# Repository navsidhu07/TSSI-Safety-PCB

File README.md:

# Tractive System Status Indicator Power & Safety Board

## Project Overview

A custom safety and fault detection PCB designed in KiCad
as part of the Formula SAE Electrical Team onboarding
project at the University of Texas at Dallas.

The PCB was designed from provided system requirements
to implement power protection, input signal conditioning,
hardware-based fault detection, and fault latching logic.

The schematic, component selection, PCB layout, and routing
were independently developed as part of the onboarding project.

## Key Features

- 12 V battery power input
- PMOS-based reverse polarity protection
- TVS diode transient voltage suppression
- 5 V voltage regulation
- BMS and IMD fault signal conditioning
- Voltage divider and RC filtering circuits
- NAND-based fault detection logic
- Hardware-based SR latch
- Power-on reset circuitry
- Custom two-layer PCB designed in KiCad

## System Architecture

### Power Distribution

```mermaid
flowchart LR
    A[12 V Battery] --> B[PMOSFET]
    B --> C[Protected 12 V Rail]
    C --- D[TVS Diode]
    C --> E[5 V Regulator]
    E --> F[5 V Rail]
    F --> G[74HC00 VCC]
    F --> H[Output Header]
```

### Fault Detection and Latching

```mermaid
flowchart LR
    A[BMS Fault] --> B[Input Terminal]
    B --> C[Voltage Divider]
    C --> D[RC Filter]

    E[IMD Fault] --> F[Input Terminal]
    F --> G[Voltage Divider]
    G --> H[RC Filter]

    D --> I[Fault Detection]
    H --> I

    I --> J[SR Latch]
    K[Reset Circuit] --> J
    J --> L[Q / Q_NOT]
    L --> M[Output Header]
```

## Hardware Design

### Power Protection and Regulation

The power input circuitry incorporates a PMOS transistor
for reverse polarity protection and a TVS diode for
transient voltage suppression. A voltage regulator
provides a 5 V supply for the digital logic circuitry.

### Input Signal Conditioning

The BMS and IMD fault inputs are conditioned using
resistive voltage dividers and RC low-pass filters.
The voltage dividers reduce the input voltage to a
logic-compatible level, while the RC filters are
intended to reduce high-frequency noise.

### Fault Detection Logic

NAND-based combinational logic processes the conditioned
BMS and IMD fault signals to determine whether a fault
condition is present.

| BMS Input | IMD Input | System Condition |
| --- | --- | --- |
| HIGH | HIGH | No Fault |
| HIGH | LOW | Fault |
| LOW | HIGH | Fault |
| LOW | LOW | Fault |

### Hardware Fault Latch

A cross-coupled NAND-based SR latch is used to retain
a detected fault condition independently of subsequent
changes in the input signals.

A power-on reset circuit is included to initialize
the latch to a defined state during startup.

## PCB Design

The schematic and PCB layout were developed in KiCad.

### Design Considerations

- Power protection and distribution
- Input voltage level conditioning
- Signal filtering
- Hardware-based fault retention
- Power supply decoupling
- Component placement and signal routing
- Separate trace widths for power and logic signals

### Schematic

### Front Copper Layer

### Back Copper Layer

The native KiCad project, schematic, and PCB layout
files are available in the [Hardware](Hardware/) directory.

Additional component libraries are provided as ZIP
archives and can be extracted and imported into KiCad
as needed.

## Design Documentation

Handwritten engineering notes developed throughout
the design process are available in the
[Documentation](Documentation/) directory.

The documentation covers:

- Fault detection truth tables
- SR latch logic and circuit development
- Input voltage conditioning
- RC filtering
- Power distribution architecture
- PCB trace width selection

## Repository Structure

```
TSSI-Safety-PCB/
├── Hardware/
│   ├── pcb1.kicad_pro
│   ├── pcb1.kicad_sch
│   ├── pcb1.kicad_pcb
│   ├── pcb1.pdf
│   ├── SMBJ13A.zip
│   └── ul_SI4143DY-T1-GE3.zip
├── Documentation/
│   └── Design-Notes.pdf
└── README.md
```

## Project Status

The component selection, schematic design, PCB layout,
and routing have been completed in KiCad as part of
the Formula SAE Electrical Team onboarding project.
The PCB has not yet been fabricated or physically
validated. Future development would involve hardware
assembly, electrical testing, and verification of
the protection and fault detection circuitry.

## Future Improvements

- Fabricate and assemble the PCB
- Validate power protection circuitry
- Verify input conditioning and logic voltage levels
- Test fault detection and latching behavior
- Validate power-on reset timing and startup behavior

## Tools and Technologies

- KiCad
- PCB Design
- Digital Logic
- MOSFET Circuitry
- Voltage Regulation
- RC Filtering
- Hardware Fault Detection
- Sequential Logic

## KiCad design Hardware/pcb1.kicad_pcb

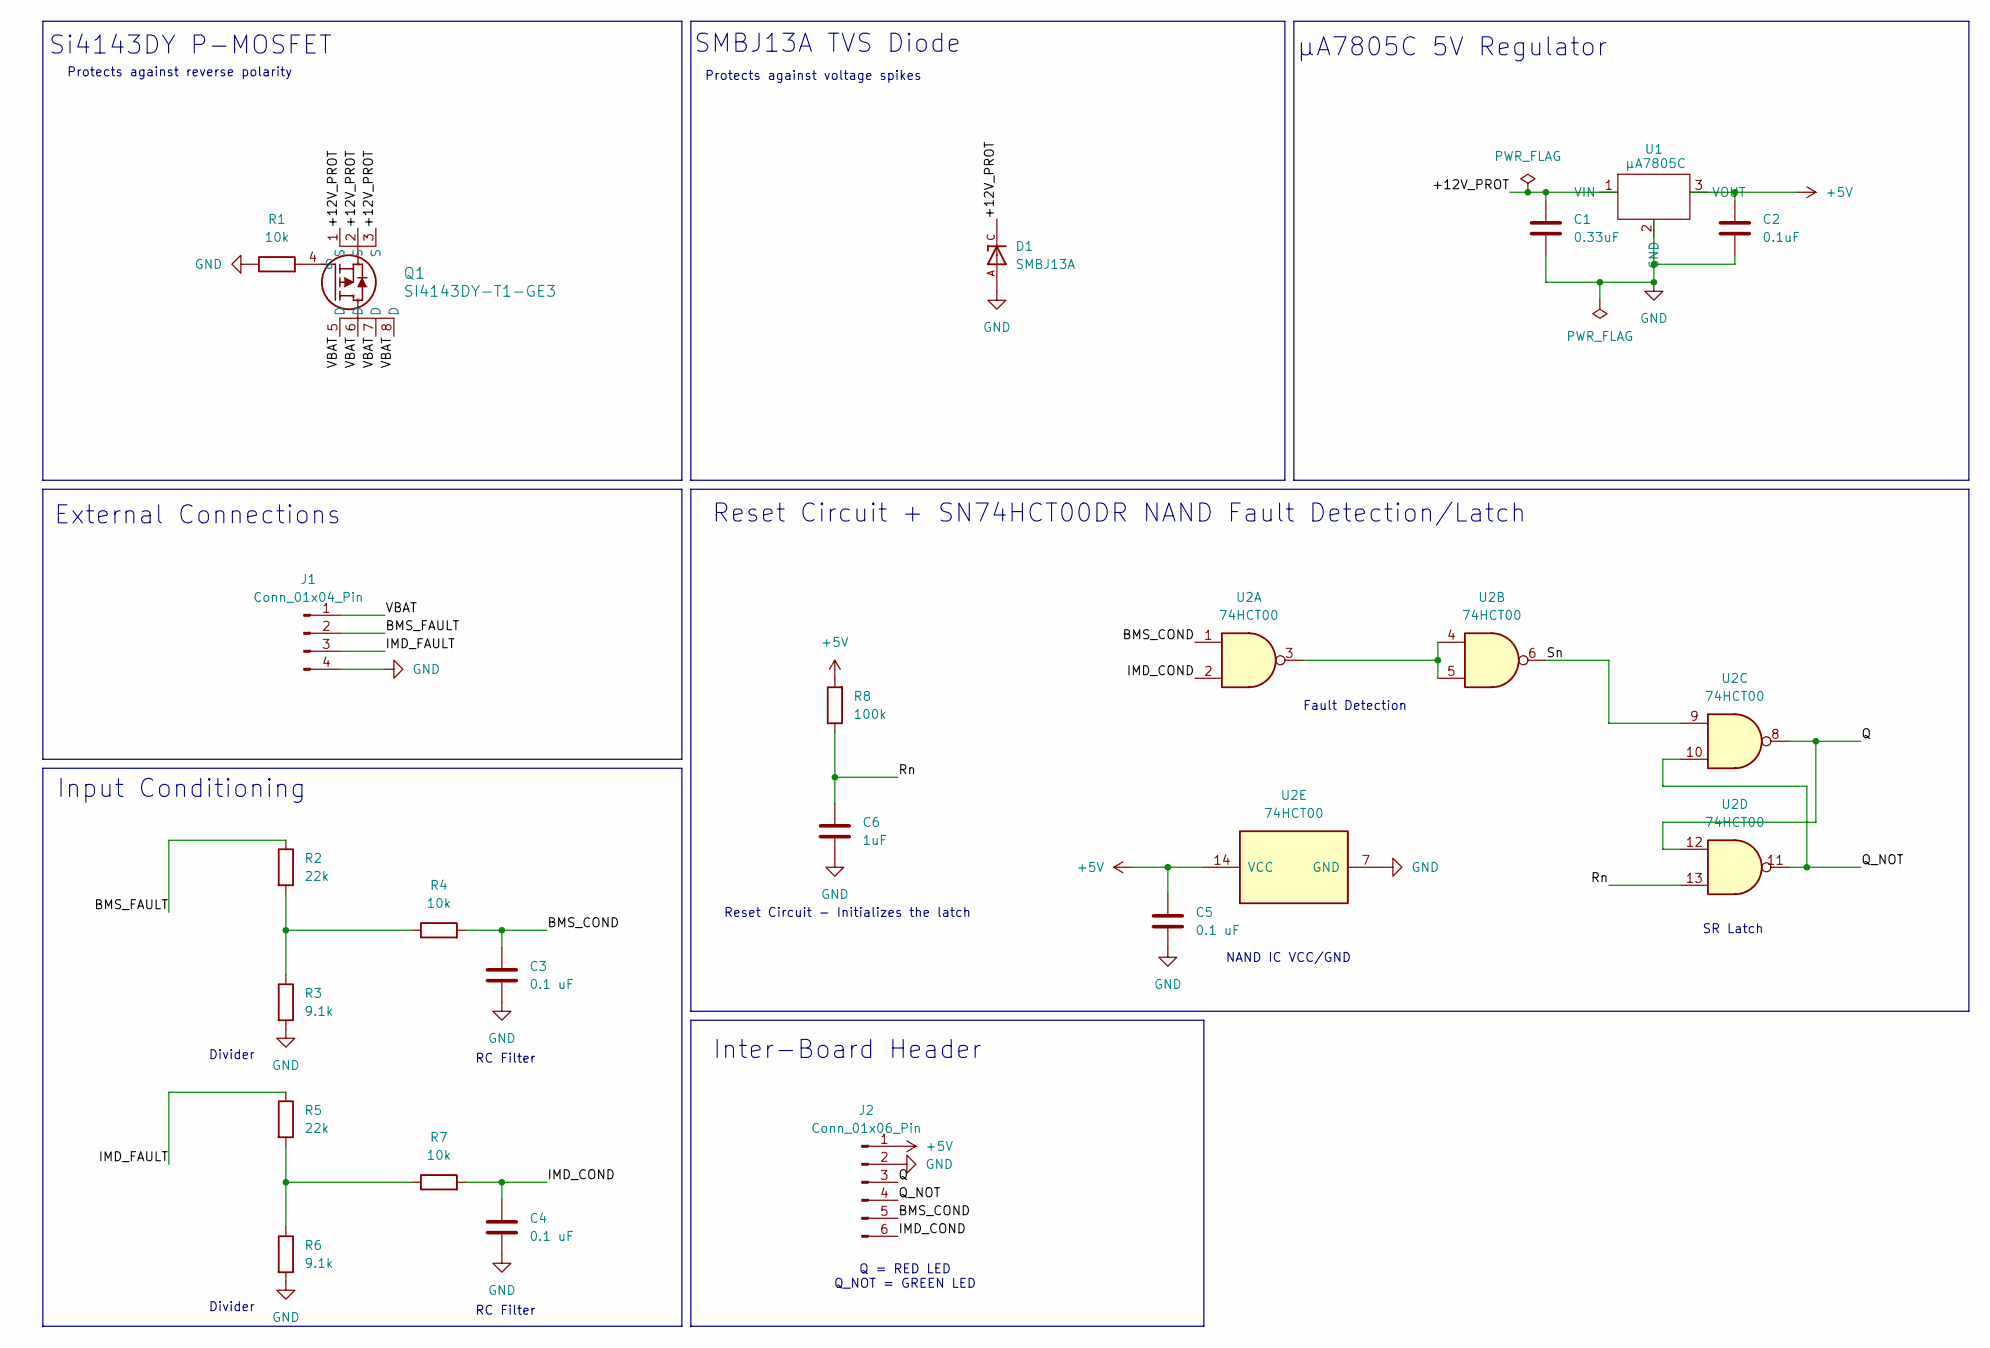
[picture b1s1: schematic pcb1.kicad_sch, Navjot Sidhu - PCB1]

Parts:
C1: 0.33uF; C_0805_2012Metric
C2: 0.1uF; C_0805_2012Metric
C3, C4, C5: 0.1 uF; C_0805_2012Metric
C6: 1uF; C_0805_2012Metric
D1: SMBJ13A; DIOM4336X265N; MPN SMBJ13A-TR
J1: Conn_01x04_Pin; PinHeader_1x04_P2.54mm_Vertical
J2: Conn_01x06_Pin; PinHeader_1x06_P2.54mm_Vertical
Q1: SI4143DY-T1-GE3; SOIC_3DY-T1-GE3_VIS
R1, R4, R7: 10k; R_0805_2012Metric
R2, R5: 22k; R_0805_2012Metric
R3, R6: 9.1k; R_0805_2012Metric
R8: 100k; R_0805_2012Metric
U1: µA7805C; TO-220-3_Vertical
U2: 74HCT00; SOIC-14_3.9x8.7mm_P1.27mm

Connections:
+5V: C2.1, C5.1, J2.1, R8.2, U1.3 (VOUT), U2.14 (VCC)
/+12V_PROT: C1.1, D1.C, Q1.1 (S), Q1.2 (S), Q1.3 (S), U1.1 (VIN)
/BMS_COND: C3.1, J2.5, R4.2, U2.1
/BMS_FAULT: J1.2, R2.1
/IMD_COND: C4.1, J2.6, R7.2, U2.2
/IMD_FAULT: J1.3, R5.1
/Q: J2.3, U2.8, U2.12
/Q_NOT: J2.4, U2.10, U2.11
/Rn: C6.1, R8.1, U2.13
/Sn: U2.6, U2.9
/VBAT: J1.1, Q1.5 (D), Q1.6 (D), Q1.7 (D), Q1.8 (D)
GND: C1.2, C2.2, C3.2, C4.2, C5.2, C6.2, D1.A, J1.4, J2.2, R1.1, R3.2, R6.2, U1.2 (GND), U2.7 (GND)
unnamed: Q1.4 (G), R1.2
unnamed: R2.2, R3.1, R4.1
unnamed: R5.2, R6.1, R7.1
unnamed: U2.3, U2.4, U2.5

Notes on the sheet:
Divider
Si4143DY P-MOSFET
Reset Circuit + SN74HCT00DR NAND Fault Detection/Latch
Q = RED LED Q_NOT = GREEN LED
Inter-Board Header
Protects against voltage spikes
Protects against reverse polarity
External Connections
NAND IC VCC/GND
Input Conditioning
Fault Detection
Reset Circuit - Initializes the latch
SMBJ13A TVS Diode
µA7805C 5V Regulator
RC Filter
SR Latch

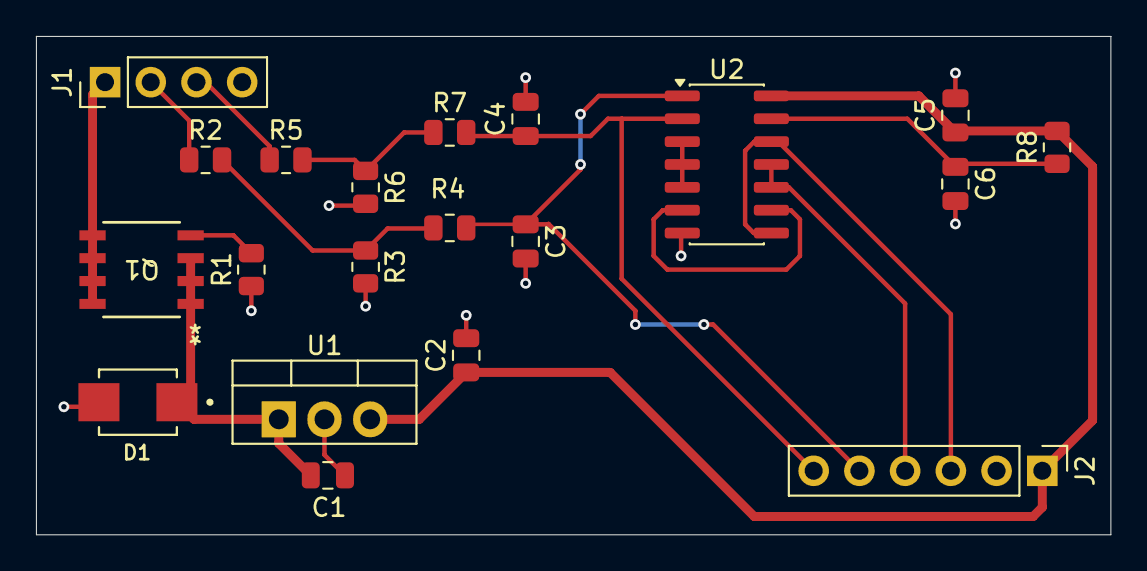
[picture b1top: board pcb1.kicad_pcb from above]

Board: 2 copper layers, 59.7 x 27.7 mm, 20 parts (0 on the bottom side), 16 nets.
